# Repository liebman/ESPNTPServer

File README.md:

# ESPNTPServer

GPS fueled ESP8266 based NTP Server

[src](src) Contains the code for the NTP Server

[eagle](eagle) contains the schematic and board designs in Eagle cad.

[enclosure](enclosure) contains the STL files for the enclosure.

This is designed around [this GPS module](https://www.amazon.com/gp/product/B075DD5746/) but any module with standard NMEA output and a pult per second signal will work if you redesign the board or use an adapter.

I also used [this display module](https://www.amazon.com/gp/product/B00O2KDQBE/).  You can use others but be careful with the power polarity, I have modules where VCC and ground pins are in a different order.

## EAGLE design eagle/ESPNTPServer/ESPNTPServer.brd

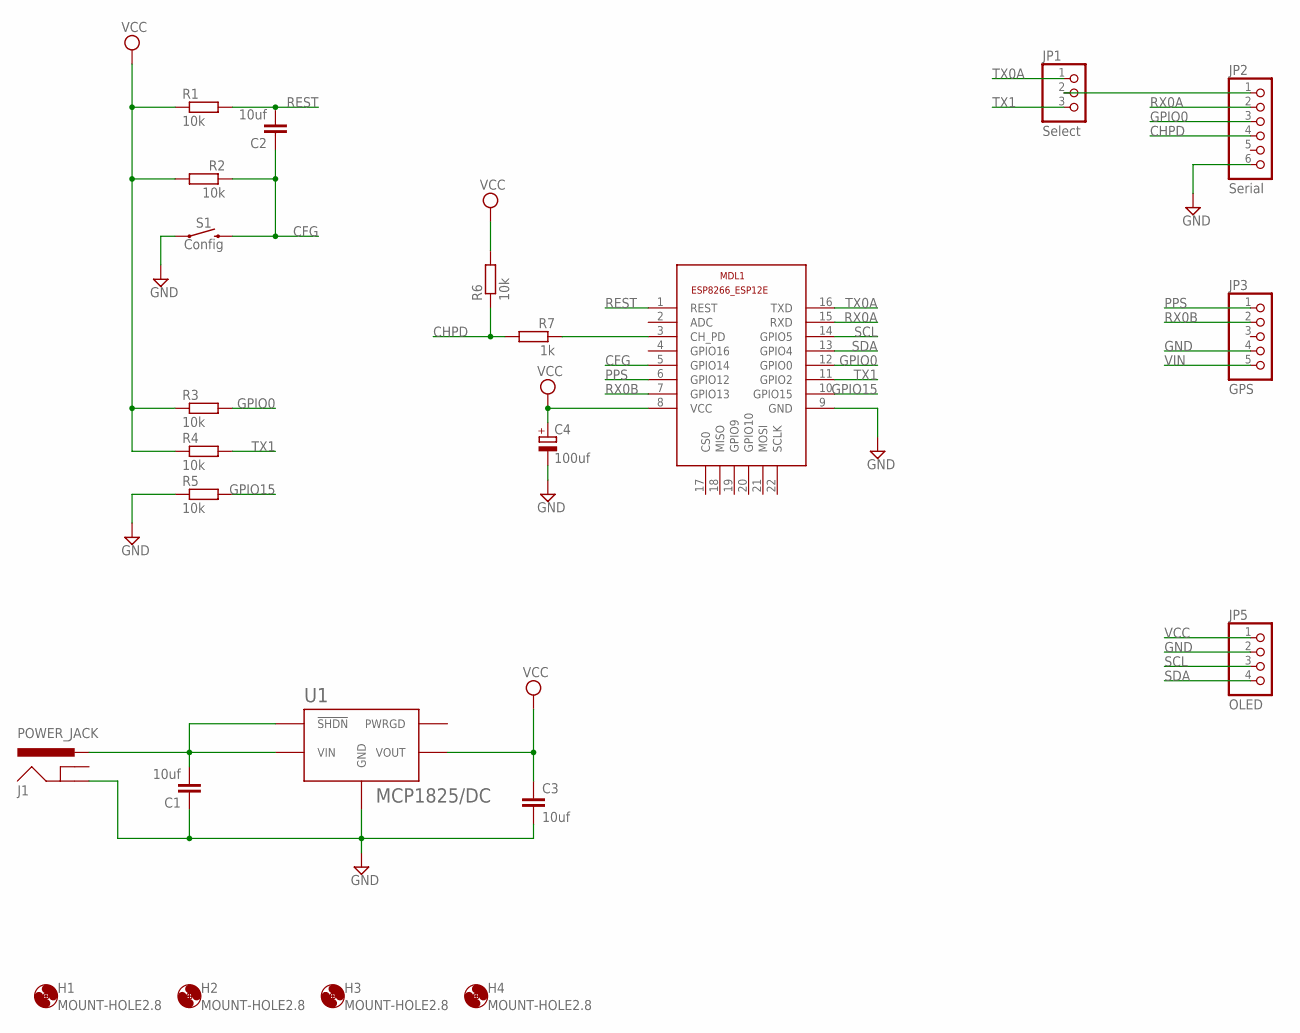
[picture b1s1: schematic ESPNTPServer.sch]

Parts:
C1, C2, C3: 10uf; C050-025X075
C4: 100uf; E2,5-5
H1, H2, H3, H4: MOUNT-HOLE2.8; 2,8
J1: POWER_JACK; POWER_JACK_PTH
JP1: Select; 1X03
JP2: Serial; 1X06
JP3: GPS; 1X05
JP5: OLED; 1X04
MDL1: ESP8266-12F; ESP8266-ESP12E
R1, R2, R3, R4, R5, R6: 10k; 0204V
R7: 1k; 0204V
S1: Config; TACTILE_SWITCH_PTH_6.0MM
U1: MCP1825/DC; SOT-223-5

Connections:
CFG: C2.1, MDL1.5 (GPIO14), R2.1, S1.3 (2)
CHPD: JP2.4, R6.1, R7.2
GND: C1.1, C3.2, C4.-, J1.GND, JP2.6, JP3.4, JP5.2, MDL1.9 (GND), R5.1, S1.1, U1.P$3 (GND), U1.P$6 (GND)
GPIO0: JP2.3, MDL1.12 (GPIO0), R3.2
GPIO15: MDL1.10 (GPIO15), R5.2
unnamed: JP1.2, JP2.1
unnamed: MDL1.3 (CH_PD), R7.1
PPS: JP3.1, MDL1.6 (GPIO12)
REST: C2.2, MDL1.1 (REST), R1.2
RX0A: JP2.2, MDL1.15 (RXD)
RX0B: JP3.2, MDL1.7 (GPIO13)
SCL: JP5.3, MDL1.14 (GPIO5)
SDA: JP5.4, MDL1.13 (GPIO4)
TX0A: JP1.1, MDL1.16 (TXD)
TX1: JP1.3, MDL1.11 (GPIO2), R4.2
VCC: C3.1, C4.+, JP5.1, MDL1.8 (VCC), R1.1, R2.2, R3.1, R4.1, R6.2, U1.P$4 (VOUT)
VIN: C1.2, J1.PWR, JP3.5, U1.P$1 (!SHDN), U1.P$2 (VIN)

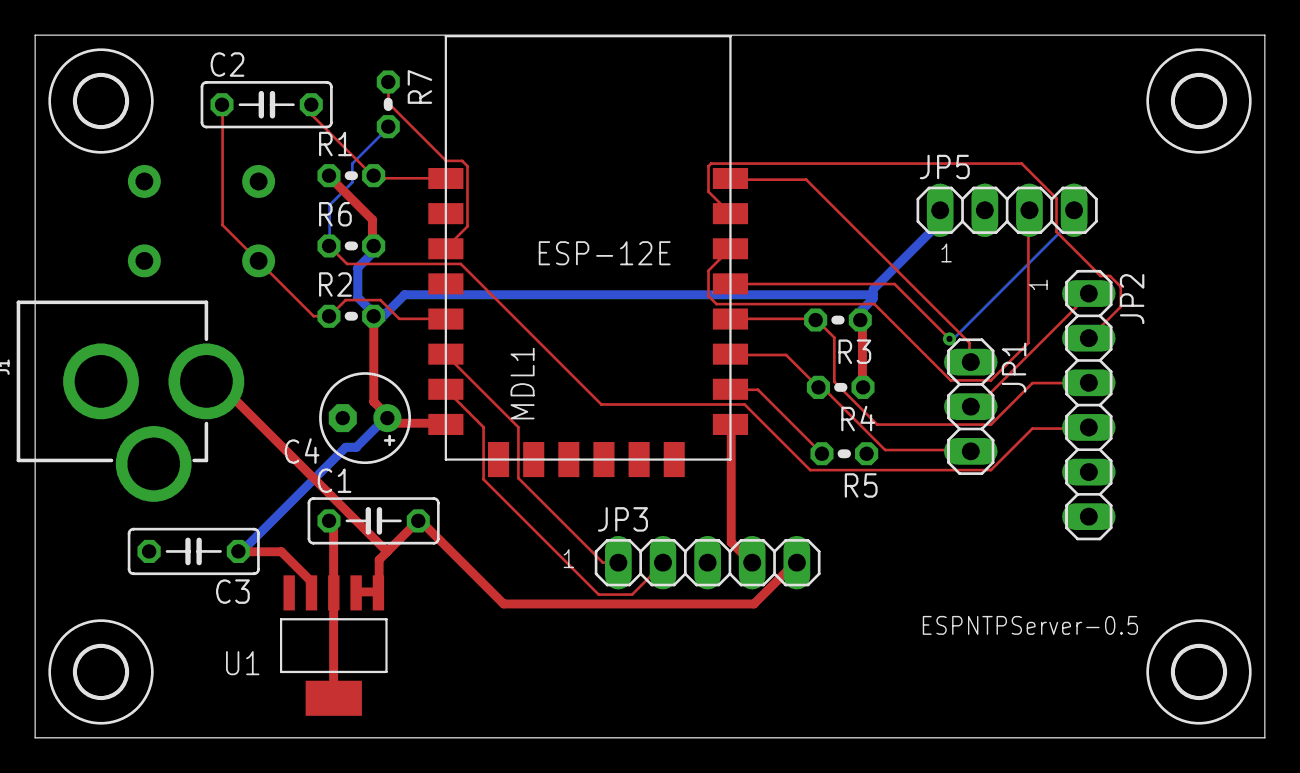
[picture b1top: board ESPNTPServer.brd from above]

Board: 2 copper layers, 70.0 x 40.0 mm, 23 parts (1 on the bottom side), 17 nets.

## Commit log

2017-11-04 Initial checkin, hacky code, using DS3231 instead of GPS unit.
2017-11-04 Update LICENSE
2017-11-05 Switch to using micros() insteam of ESP.getCycleCount()
2017-11-11 switch to adafruit ultimate GPS, drop all the DS3231 rtc junk
2017-11-12 Lots of debugging and experimentation going on!
2017-11-12 add free heap to the display and output
2017-11-13 we are not valid until 60 PPS cycles after we have a valid gps
2018-01-27 Initial esp-idf based implentation
2018-01-27 move minmea to component
2018-01-27 fix upstream
2018-01-28 added esp32-snippets as submodule, added special component.mk to only grap the u8g2 hooks
2018-01-28 update README for existance of submodules
2018-01-28 add config options for debug level for each task, default to info
2018-01-28 config for u8g2_hal logging
2018-03-03 switched back to esp8266 and use Serial1 for debug output and Serial for GPS
2018-03-03 missed update logging change for WireUtils
2018-03-05 refactor display
2018-03-05 display seconds "till valid"
2018-03-08 seperate time setting from validity check, if we chaneg the time we also invalidate
2018-03-12 Switch to use DLog as dbug output
2018-05-27 minor changes - invert display due to current hardware layout mistake
2018-05-27 reorg to include core and librany deps in project using submodules
2018-05-27 added script to insure submodules and such are setup
2018-06-05 added OTA update support and started on syslog logging
2018-06-05 use stdfun branch
2018-06-06 added platdform hack for sloeber
2018-06-07 cleanup warnings in oled
2018-06-11 added syslog logging support & Config saving via SPIFFS/Json file
2018-06-11 start travis builds
2018-06-11 fix repo urls
2018-06-11 DebugLevel
2018-06-11 back to masyter branch
2018-06-11 remove local hack to fix build
2018-06-12 added eagle designs
2018-06-12 added enclosure
2018-06-13 rotate images
2018-06-13 update images
2018-06-13 images
2018-06-13 Reorg (#1)
    * reorg to include core and librany deps in project using submodules
    * added script to insure submodules and such are setup
    * added OTA update support and started on syslog logging
    * added syslog logging support & Config saving via SPIFFS/Json file
    * start travis builds
    * DebugLevel
2018-06-13 fix travis link
2018-06-16 corrected image
2018-06-17 cleanup syslog & devicename
2018-06-19 added version, updated WiFiManager
2018-08-18 updated esp8266 core & WiFiManager
2018-08-18 updated version
2019-07-18 setup build for platformio
2019-07-18 update type for fonts (char* -> uint8_t*)
2019-07-18 support CertStore
2019-07-18 updates for change to platformio
2019-07-18 remove submodules
2019-07-18 remove git submodules
2019-07-18 remove setup.sh - not needed wit platformio
2019-07-18 platformio
2019-07-19 change the Config.json path to include leading "/" so that a default config can optionally be supplied in an initial SPIFFS image
2019-07-19 add support for ssl certificate bundle with bleading edge esp8266 Arduino core
2019-07-19 remove missed merge marker
2019-09-06 - set version to 1.0.2 - change CPU freq 160MHz - use WIFI_NONE_SLEEP - cleanup warnings
2019-09-06 fix build indicator link
2019-12-31 only bring up the config portal if there is no config file or config button is held
2019-12-31 use slightly older version of WiFiManager
2020-01-04 Disable auto captive portal when configuration exists (#5)
    * only bring up the config portal if there is no config file or
    config button is held
    * use slightly older version of WiFiManager
